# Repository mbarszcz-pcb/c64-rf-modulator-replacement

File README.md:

# c64-rf-modulator-replacement
C64 Composite/S-Video RF Modulator Replacement

## Quick Links
* [Schematic](pdf/c64-rf-modulator-replacement-schematic.pdf)

* [Gerber Files](gerbers)

* [PCB Renderings](images/pcb)

* [Photos](images/photos)

# Introduction 
This is my version of a C64 RF Modulator replacement based on the schematics of similar designs like [Zero-X/OMS's Modified Commodore RF Modulator Design](images/zerox-oms-modulator_simple-schematic.png) and [JMP$FCE2's S-Video only design](images/jmp$fce2-schematic.png).  This board can be used to replace a damaged or defective RF modulator in your C64, to improve the sharpness of your video output, or as a modern solution to replace the composite/luma/chroma output functionality of the original modulator on new motherboards such as the SixtyClone or Bwack’s KU-14194.

This design has a few goals that set it apart from the others:

1.	It is a universal solution that fits and is electrically compatible with both the C64 and C64C without having to change components on the board or run jumper wires for power.

2.	It is easy and inexpensive to build with only a single, small PCB and all through-hole components.

3.	It provides [high quality S-Video (Y/C) output](images/photos/video-output-6569-r5.png) while maintaining composite video output for compatibility.

4.  It provides adjustable luma/chroma output levels to fine-tune the S-video signal. This allows for the best possible compatibility with a wide variety of different board revisions, VIC chips, aging components and monitors. Adjustable levels  mean this board can also be used with s-video cables with or without an inline resistor to eliminate “checkerboarding” caused by too high of a chroma level.

# Compatibility
This RF modulator replacement is compatible with motherboard revisions 250407, 250425, 250466, and 250469, and both NTSC and PAL VIC-II chips. I have not tested it, but I believe it should also be compatible with Bwack's KU-14194 board as well since it uses the standard longboard RF modulator. It is not compatible, however, with the early revision 326298-01 boards with the 5 Pin AV Output. This revision uses a different modulator pin layout, and the video signals are not combined in the modulator. They are instead processed with discrete components inside the VIC-II can.

# Gathering the components
Kicad files are available for you to view or modify as you see fit. Gerber files are available that can be uploaded directly to your favorite PCB fab to make your own boards, and a complete Bill of Materials (BOM) can be found [here](c64-rf-modulator-replacement-bom.xlsx) with example parts from Digikey. At the time of writing this, the components cost about $12 US, not including the PCB or shipping.

I strongly recommend building the entire board, if you choose to do so, there are a few components that can be omitted in different situations to decrease the cost at the expense of features and flexibility.

## Trimmers
The trim pots used to adjust the luma and chroma are the most expensive components in this project. I highly recommend using them, but if you choose, you may jumper the solder bridges on the back of the board to bypass the trimmer pads and install 150 Ohm resistors for R4 and R7. This won't give you the precision adjustment of the trimmers, but it will be close enough for most configurations. You can experiment with different fixed value resistors between 100-1K Ohm if you want to change fixed output levels.

## No Composite Video
I have not seen any improvement in S-video quality by omitting the composite video components, but if you really don’t want composite output, L2, R8, R11, and C6 can be omitted from the build.

## No Voltage Regulator
If you are only ever going to use the RF modulator replacement on a C64C 250469 short board, you don’t need the voltage regulator or the input/output capacitors since 5V is provided directly to the modulator on pin 1. This means you can omit C3, C5, C7, C8, and U1 from the build.

# Building the board
Once you have your PCBs and all your components, soldering them together should be pretty straightforward. You can use the schematic or the BOM to place the right value parts in the right place. From a soldering standpoint, it is easiest to assemble the components starting with the lowest profile first and then work your way up. This would be mean soldering the resistors and inductor first, then the ceramic caps, the diode, electrolytic capacitors, transistors and voltage regulator, and finally, the jumper block. The jumpers can then be installed on the headers in the appropriate configuration. Finish off by removing the flux residue with some cotton swabs or a brush and isopropyl alcohol.

# Installing the board
First, you need to remove the old RF modulator. This can be a bit tricky as the large metal can will suck the heat right out of the iron. I can’t help you much here, but I can only suggest you use a soldering iron with plenty of heat, use a wide tip, to take your time, and don't rip off any traces. The new board can then be installed one of two ways.

The first is soldering it directly to the motherboard. For this, you can solder two .1” pin headers into the motherboard (making sure they are straight) and then setting the RF modulator replacement down on top of them. I recommend sticking small rubber feet near the rear of the board to help support it. You can slide two feet under the front of the rf modulator replacement to keep the pcb level and evenly spaced all the way around while you solder the headers from the top side. Trim the excess length of the header pins off and slide out the rubber feet. For a nicer finish, reflow the solder joints after you have trimmed them.

Alternatively, you can make the replacement a bit more modular by soldering two 4-pin female headers on the motherboard and two 4-pin male headers on the RF modulator replacement. This will allow you to plug and unplug the modulator easily. It is not required, but as the board will be approximately ½” above the motherboard and “hanging” on the headers, you may want to use some rubber feet, foam, or double-sided tape as a spacer to support the back of the board.

# Adjustments

## Configuring the mainboard
If you are using the longboard (Rev 250407, 250425, 240441, 250466) it is important to make sure the G.PAL/I.PAL jumper by the modulator is SHORTED, or the ground pin the modulator replacement attaches to will be floating and will not work correctly.  You can validate this by checking continity between the left most RF modulator through-hole on the C64 motherboard and a suitable ground point on the C64 motherboard (Cartridge shield, plated edge of the moatherboard, 5V Regulator heatsink, etc).  If the modulator is installed, you can also check continutiy between the bottom left pin on the jumper block and a suitable ground point.

## Jumper Settings
The adjustment of the jumpers routes the signals to the proper pinout for the motherboard you are using, switches the correct pull-up resistor for the VIC-II luma, and enables or disables the use of an onboard 5V regulator.With all jumpers in the up position, the board is configured for use on the 12V C64 “longboards” (250407, 250425, and 250466). In this configuration, the 5V regulator is used to regulate the 9V Unregulated power on pin 1 down to 5V

With all jumpers in the down position, the board is configured for use on the 250469 “short board” commonly found in the C64C. In this configuration, the 5V input on pin 1 is fed directly in the circuit without the need for the 5V regulator. Be sure you are using a short board if all the jumpers are down, or you could accidentally fry your VIC-II by accidentally feeding it 9V unreg from a long board.

For most configurations, the jumpers should be either all up or all down; however if you understand what you are doing and want to run a 5V 856x VIC-II from a short board in a 12V long board, there is one jumper that you may want to run in a non-standard configuration. First, you MUST isolate pin 13 on the VIC-II socket from the VIC-II (the short board outputs 12V there while an 856x is expecting 5V). Pin 13 on the VIC-II can then be connected to pin 40 (which is 5V Vcc). I recommend not modifying the VIC-II chips but instead using a piggyback socket or PCB. With a standard machined pin socket, simply trim off leg 13 and solder a jumper wire from leg 13 to 40. The 856x VIC-II can then just plug into the socket without any damaging modifications. Once the VIC-II is installed, the jumpers on the RF modulator should be in the following configuration to use the correct short board 1K pullup resistor:

## Adjusting the Output Level
If you choose to include adjustable potentiometers in your build, a counter-clockwise adjustment on the luma (Y) and chroma (C) potentiometers will reduce the output level. A clockwise adjustment will increase the output level. My recommendation is to start with both adjustments fully counter-clockwise and increase as necessary. The levels can be set with a scope or simply “by eye” depending on the tools you have available.

An ideal chroma signal should be ~300mV peak-to-peak. The adjustment on the board should allow you to adjust it from approximately ~250mV - 1.7V. This range allows you to dial back the output for use with a standard S-video cable or to turn it up to compensate for the cables with the inline 330-1K resistor. Some monitors don't care if the signal is too hot, others will give you an ugly checkered pattern (especially LCDs). If you don't have an oscilloscope to measure the peak-to-peak voltage, start with the chroma pot fully counter-clockwise and increase it until the colors are sufficiently saturated. If you go too far, the image will begin to look “grainy” or have a checkerboard pattern.

Officially, an ideal luma signal should be 1V PP (including the sync pulse). Depending on the output of the VIC-II chip you are using, the adjustment on the board should allow you to adjust it from approximately ~575mV-1.5V PP. The original breadbins output a signal around 1.2V PP, while the later C64Cs were closer to an “in-spec” 1V PP. On some monitors though 1V PP can look too look dark (requiring you to turn up the contrast on your monitor). If using a scope, I would adjust it to approximately 1.1V PP.  If adjusting by eye, start  low and increase the level until the light blue text is reasonably legible against the dark blue background. If the border and text start to look “white” you have gone too far. Another good test on a CRT is white text on a black background. If the white text is blooming, you should back the signal off. The effect will be very similar to having the contrast set too high.

Composite video output remains at a fixed output level regardless of the Y and C adjustment pots.

# A note on use with LCD Monitors and Checkerboarding
If you are still getting checkerboarding even after adjusting the potentiometers, try soldering a 330pF Resistor (you can experiement with different values to see what works best with your setup) across R3 (the resistor on the top right corner of the board).  This combines with R3 to create an RC filter that seems to help eliminate this.  There seems to be a degree of variablility regarding different A->D conversion cirtuitry used in different brands of LCD monitors and in devices like the RetroTink2X or OSSC that makes some displays more susceptable to checkerboarding.  From what I've been able to see, CRT monitors are not susceptable to this behavior.

# Changelog
Rev A – 2020-03-15 - Prototype

Rev B – 2020-03-25 - Initial production revision, fixed schematic bugs, tweaked values and removed unnecessary components to improve picture quality

Rev C – 2020-04-05 - Adjusted positioning of several traces, vias, and regulator U1 to improve physical spacing. Changed RV1 and RV2 for "W" footprint trimmers with inline legs due to parts availability. Swapped R4 and R5 physical locations to better accomodate the new pin configuration

Rev D – 2020-04-07 - Adjusted power and ground trace thickness, added additional vias, added custom trimmer footprint to ID proper placement, optimized ground pours, increased chroma/luma/power trace isolation

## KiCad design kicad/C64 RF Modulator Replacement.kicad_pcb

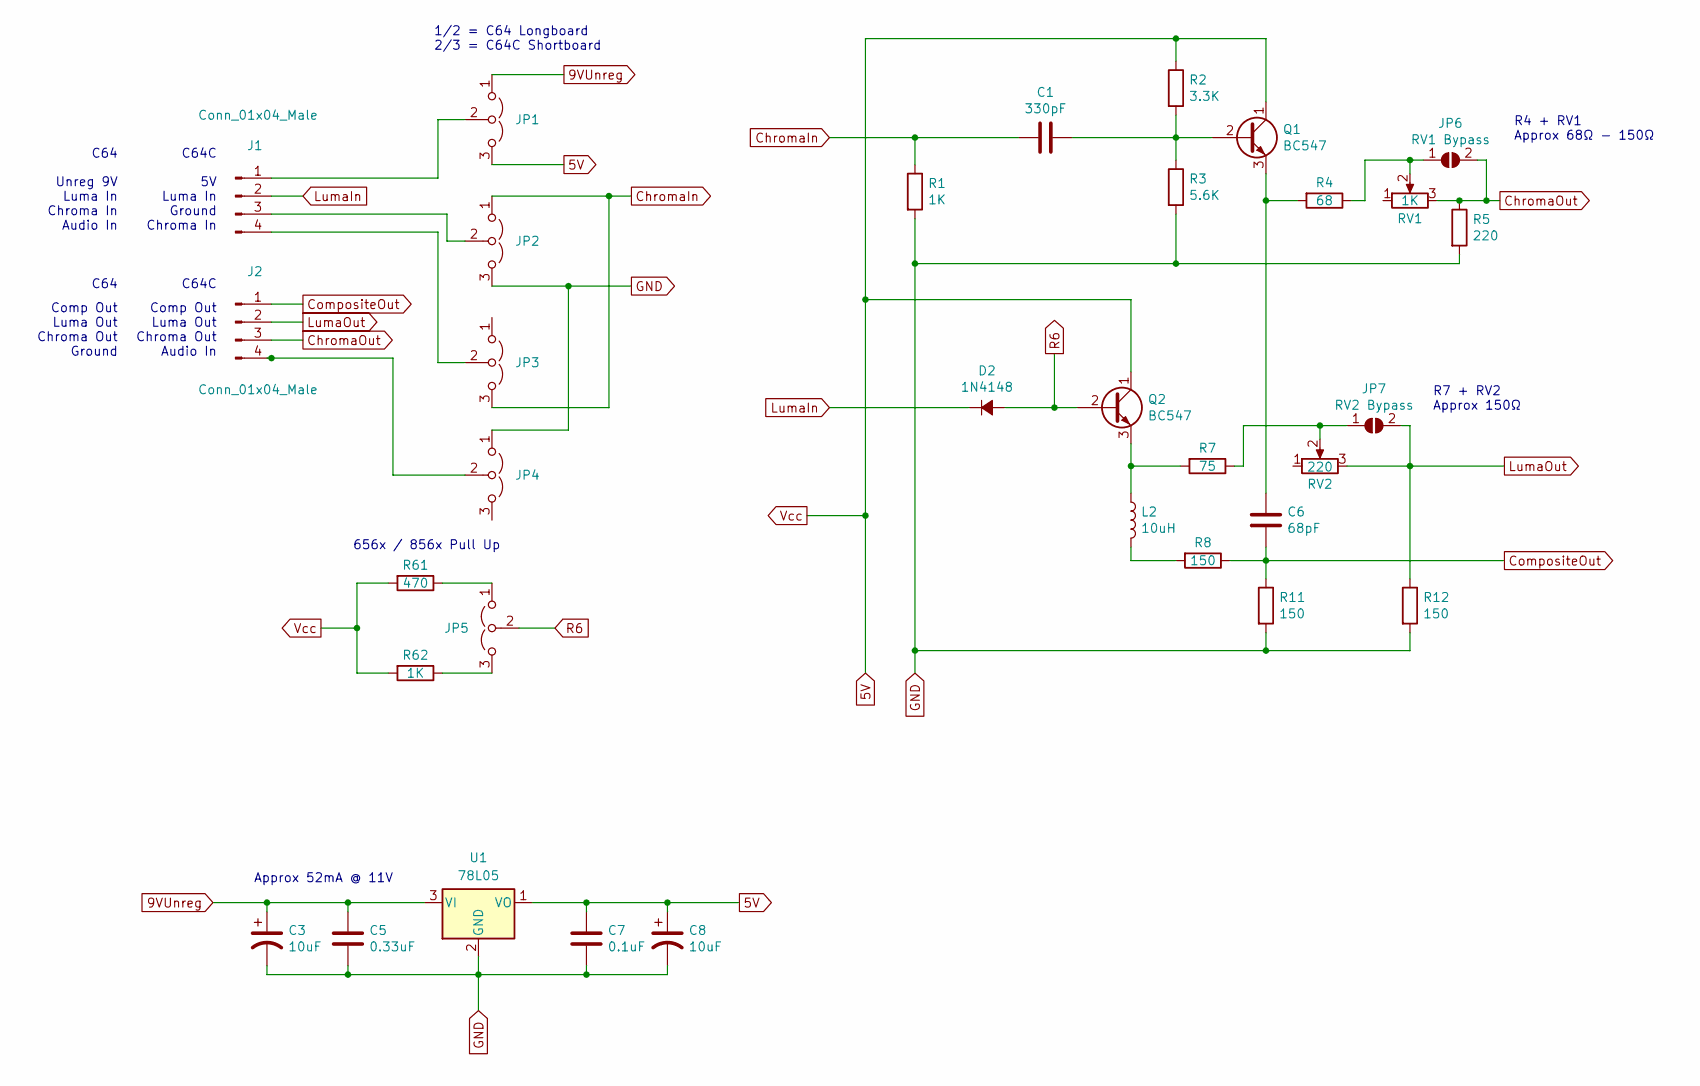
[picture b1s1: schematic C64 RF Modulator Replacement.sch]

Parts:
C1: 330pF; C_Disc_D5.0mm_W2.5mm_P2.50mm
C3, C8: 10uF; CP_Radial_D5.0mm_P2.50mm
C5: 0.33uF; C_Disc_D5.0mm_W2.5mm_P2.50mm
C6: 68pF; C_Disc_D5.0mm_W2.5mm_P2.50mm
C7: 0.1uF; C_Disc_D5.0mm_W2.5mm_P2.50mm
D2: 1N4148; D_DO-35_SOD27_P2.54mm_Vertical_KathodeUp
J1, J2: Conn_01x04_Male; PinHeader_1x04_P2.54mm_Vertical
JP1, JP2, JP3, JP4, JP5: Jumper_3_Open; PinHeader_1x03_P2.54mm_Vertical-NoSilk
JP6: RV1 Bypass; SolderJumper-2_P1.3mm_Open_RoundedPad1.0x1.5mm
JP7: RV2 Bypass; SolderJumper-2_P1.3mm_Open_RoundedPad1.0x1.5mm
L2: 10uH; L_Axial_L6.6mm_D2.7mm_P10.16mm_Horizontal_Vishay_IM-2
Q1, Q2: BC547; TO-92_HandSolder
R1, R62: 1K; R_Axial_DIN0207_L6.3mm_D2.5mm_P10.16mm_Horizontal
R2: 3.3K; R_Axial_DIN0207_L6.3mm_D2.5mm_P10.16mm_Horizontal
R3: 5.6K; R_Axial_DIN0207_L6.3mm_D2.5mm_P10.16mm_Horizontal
R4: 68; R_Axial_DIN0207_L6.3mm_D2.5mm_P10.16mm_Horizontal
R5: 220; R_Axial_DIN0207_L6.3mm_D2.5mm_P10.16mm_Horizontal
R7: 75; R_Axial_DIN0207_L6.3mm_D2.5mm_P10.16mm_Horizontal
R8, R11, R12: 150; R_Axial_DIN0207_L6.3mm_D2.5mm_P10.16mm_Horizontal
R61: 470; R_Axial_DIN0207_L6.3mm_D2.5mm_P10.16mm_Horizontal
RV1: 1K; Potentiometer_Bourns_3296W_Vertical
RV2: 220; Potentiometer_Bourns_3296W_Vertical
U1: 78L05; TO-92_HandSolder

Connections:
5V: C7.1, C8.1, JP1.3 (B), Q1.1 (C), Q2.1 (C), R2.1, R61.2, R62.2, U1.1 (VO)
9VUnreg: C3.1, C5.1, JP1.1 (A), U1.3 (VI)
ChromaIn: C1.1, JP2.1 (A), JP3.3 (B), R1.1
ChromaOut: J2.3, JP6.2 (B), R5.1, RV1.3
CompositeOut: C6.2, J2.1, R8.1, R11.1
GND: C3.2, C5.2, C7.2, C8.2, JP2.3 (B), JP4.1 (A), R1.2, R3.2, R5.2, R11.2, R12.2, U1.2 (GND)
LumaIn: D2.1 (K), J1.2
LumaOut: J2.2, JP7.2 (B), R12.1, RV2.3
unnamed: C1.2, Q1.2 (B), R2.2, R3.1
unnamed: C6.1, Q1.3 (E), R4.2
unnamed: J1.1, JP1.2 (C)
unnamed: J1.3, JP2.2 (C)
unnamed: J1.4, JP3.2 (C)
unnamed: J2.4, JP4.2 (C)
unnamed: JP5.1 (A), R61.1
unnamed: JP5.3 (B), R62.1
unnamed: JP6.1 (A), R4.1, RV1.2
unnamed: JP7.1 (A), R7.1, RV2.2
unnamed: L2.1, Q2.3 (E), R7.2
unnamed: L2.2, R8.2
R6: D2.2 (A), JP5.2 (C), Q2.2 (B)

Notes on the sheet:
Unreg 9V Luma In Chroma In Audio In
Comp Out Luma Out Chroma Out Ground
5V Luma In Ground Chroma In
Comp Out Luma Out Chroma Out Audio In
C64
C64C
1/2 = C64 Longboard 2/3 = C64C Shortboard
656x / 856x Pull Up
Approx 52mA @ 11V
R4 + RV1 Approx 68Ω - 150Ω
R7 + RV2 Approx 150Ω

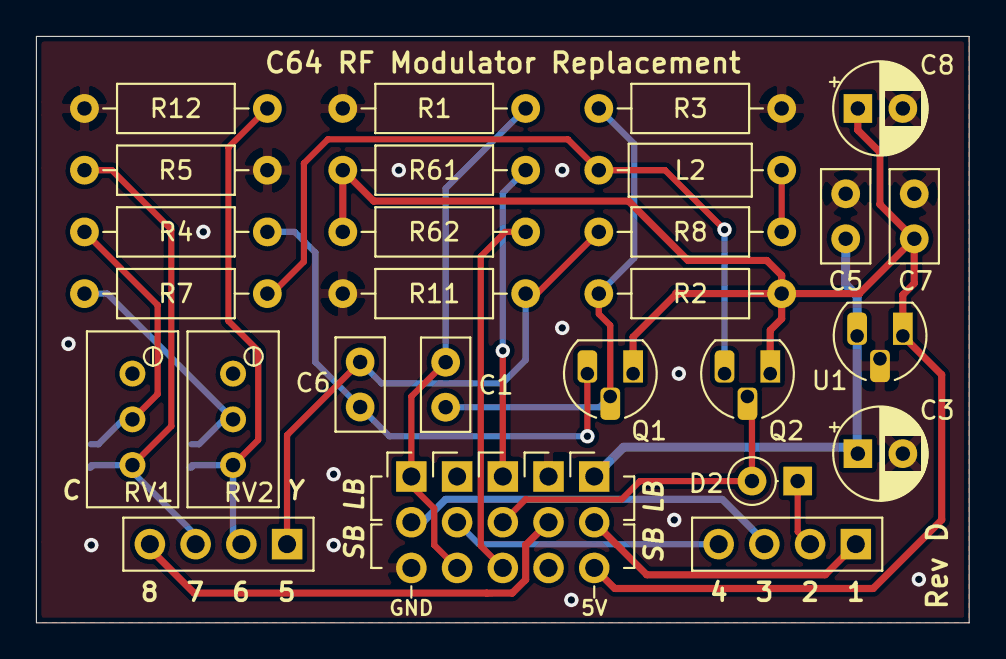
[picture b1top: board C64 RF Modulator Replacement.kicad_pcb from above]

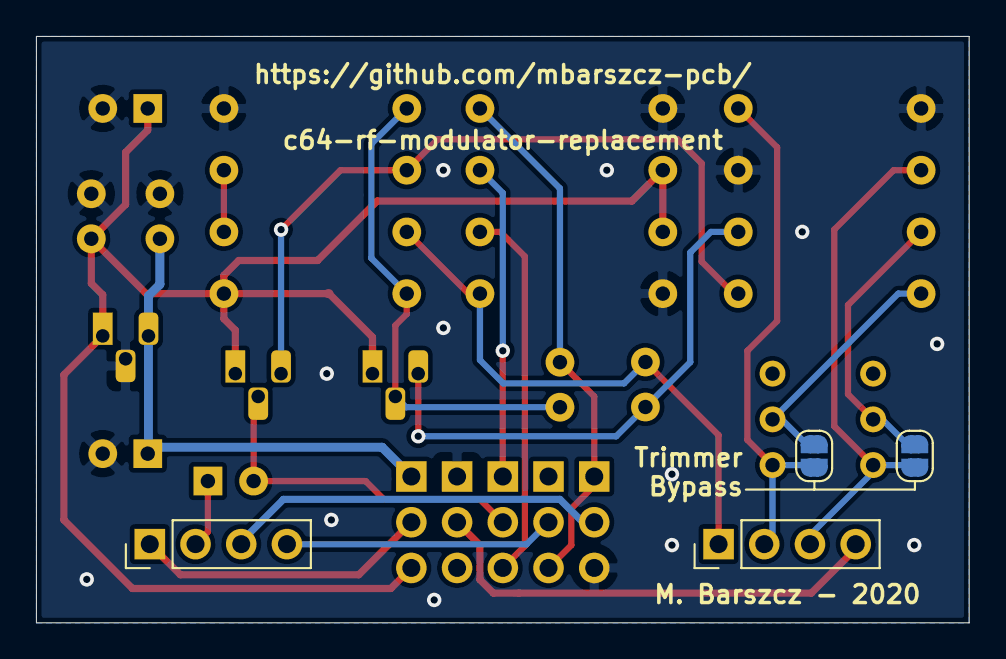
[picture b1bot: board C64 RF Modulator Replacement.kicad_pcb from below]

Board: 2 copper layers, 51.8 x 32.6 mm, 33 parts (4 on the bottom side), 21 nets.

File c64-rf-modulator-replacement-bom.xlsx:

Quantity | Customer Reference | Description | Digi-Key Part Number | Digi-Key Description | Manufacturer | Manufacturer Part Number | Notes
1 | C1 | 330pF Ceramic Capacitor | 478-11694-ND | CAP CER 330PF 100V C0G/NP0 RAD | AVX Corporation | SR151A331JAA
1 | C5 | 0.33uF Ceramic Capacitor | 478-5733-ND | CAP CER 0.33UF 50V Z5U RADIAL | AVX Corporation | SR205E334MAR
1 | C6 | 68pF Ceramic Capacitor | 478-5215-ND | CAP CER 68PF 100V NP0 RADIAL | AVX Corporation | SR151A680JAR
1 | C7 | 0.1uF Ceramic Capacitor | 478-3192-ND | CAP CER 0.1UF 50V Z5U RADIAL | AVX Corporation | SR205E104MAR
2 | C3,C8 | 10uF Electrolytic Capacitor | 493-17440-1-ND | CAP ALUM 10UF 20% 25V RADIAL | Nichicon | USV1E100MFD1TP
1 | L2 | 10uHH Inductor | M10135-ND | FIXED IND 10UH 370MA 750 MOHM TH | Bourns Inc. | 78F100J-RC
1 | D2 | 1N4148 Diode | 1N4148FS-ND | DIODE GEN PURP 100V 200MA DO35 | ON Semiconductor | 1N4148
2 | R1,R62 | 1K Ohm 1/4W Resistor | CF14JT1K00CT-ND | RES 1K OHM 1/4W 5% AXIAL | Stackpole Electronics Inc | CF14JT1K00
1 | R2 | 3.3K Ohm 1/4W Resistor | CF14JT3K30CT-ND | RES 3.3K OHM 1/4W 5% AXIAL | Stackpole Electronics Inc | CF14JT3K30
1 | R3 | 5.6K Ohm 1/4W Resistor | CF14JT5K60CT-ND | RES 5.6K OHM 1/4W 5% AXIAL | Stackpole Electronics Inc | CF14JT5K60
1 | R4 | 68 Ohm 1/4W Resistor | CF14JT68R0CT-ND | RES 68 OHM 1/4W 5% AXIAL | Stackpole Electronics Inc | CF14JT68R0
1 | R5 | 220 Ohm 1/4W Resistor | CF14JT220RCT-ND | RES 220 OHM 1/4W 5% AXIAL | Stackpole Electronics Inc | CF14JT220R
1 | R7 | 75 Ohm 1/4W Resistor | CF14JT75R0CT-ND | RES 75 OHM 1/4W 5% AXIAL | Stackpole Electronics Inc | CF14JT75R0
3 | R8,R11,R12 | 150 Ohm 3/4W Resistor | CF14JT150RCT-ND | RES 150 OHM 1/4W 5% AXIAL | Stackpole Electronics Inc | CF14JT150R
1 | R61 | 470 Ohm 1/4W Resistor | CF14JT470RCT-ND | RES 470 OHM 1/4W 5% AXIAL | Stackpole Electronics Inc | CF14JT470R
1 | RV1 | 1K Ohm 25 Turn Trimpot - Chroma Adjustment (Triangular pin configuration) | 3296Y-102LF-ND | TRIMMER 1K OHM 0.5W PC PIN TOP | Bourns Inc. | 3296Y-1-102LF | If omitted, use 150 Ohm R4
1 | RV2 | 200 Ohm 25 Turn Trimpot - Luma Adjustment (Triangular pin configuration) | 3296Y-201LF-ND | TRIMMER 200 OHM 0.5W PC PIN TOP | Bourns Inc. | 3296Y-1-201LF | If omitted, use 150 Ohm R72 250 Ohm Trimmer Preferred, but may use 200 Ohm if t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
2 | Q1,Q2 | BC547B NPN Transistor | BC547BFS-ND | TRANS NPN 45V 0.1A TO-92 | ON Semiconductor | BC547B
1 | U1 | 5V 78L05 Linear Regulator | 497-7268-ND | IC REG LINEAR 5V 100MA TO92-3 | STMicroelectronics | L78L05CZ
1 | 3x5 Jumper Block | 3x5 Pin Header | SAM12316-ND | CONN HEADER VERT 15POS 2.54MM | Samtec Inc. | TSW-105-07-F-T
5 | Jumpers | 0.1" Jumpers | S9337-ND | CONN JUMPER SHORTING .100" GOLD | Sullins Connector Solutions | QPC02SXGN-RC

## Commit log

2020-04-05 intial upload
2020-04-05 rearranged folder structure
2020-04-05 rename images dir
2020-04-05 new images
2020-04-05 organized images
2020-04-05 Rev C
2020-04-05 moved gerbers, updated title image
2020-04-05 Create LICENSE
2020-04-07 Rev D
2020-04-07 uploaded revD pcbway
